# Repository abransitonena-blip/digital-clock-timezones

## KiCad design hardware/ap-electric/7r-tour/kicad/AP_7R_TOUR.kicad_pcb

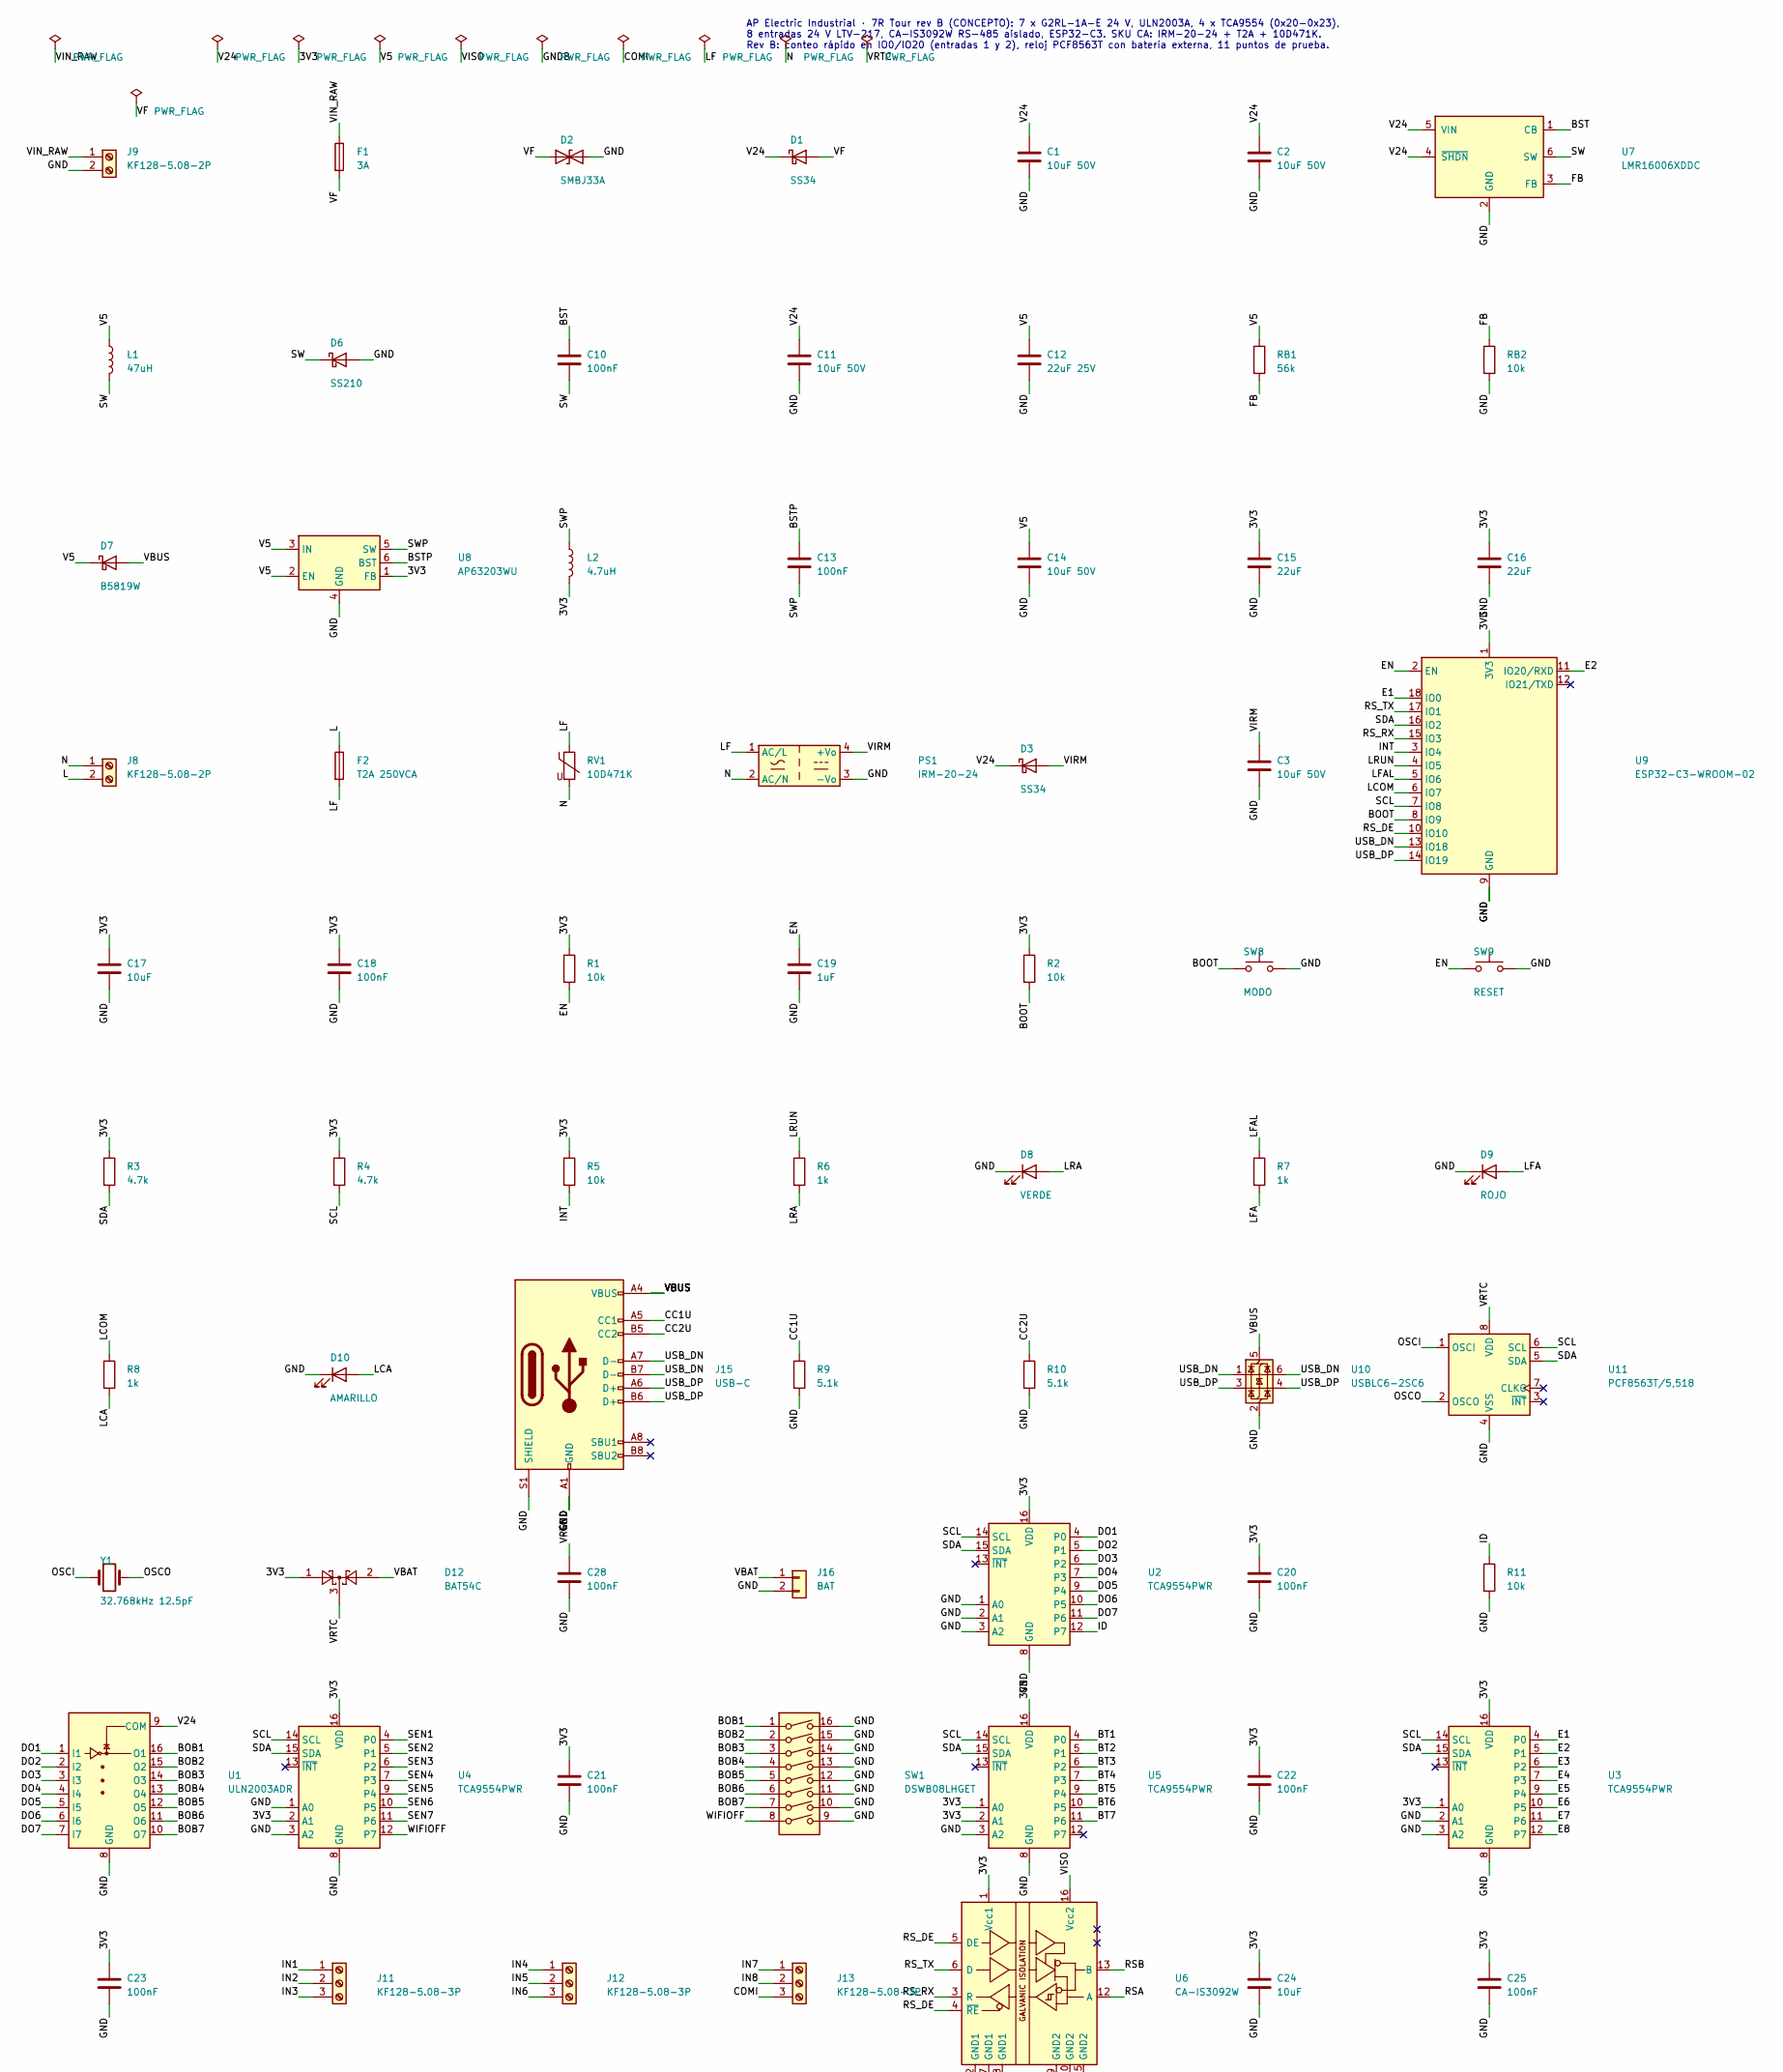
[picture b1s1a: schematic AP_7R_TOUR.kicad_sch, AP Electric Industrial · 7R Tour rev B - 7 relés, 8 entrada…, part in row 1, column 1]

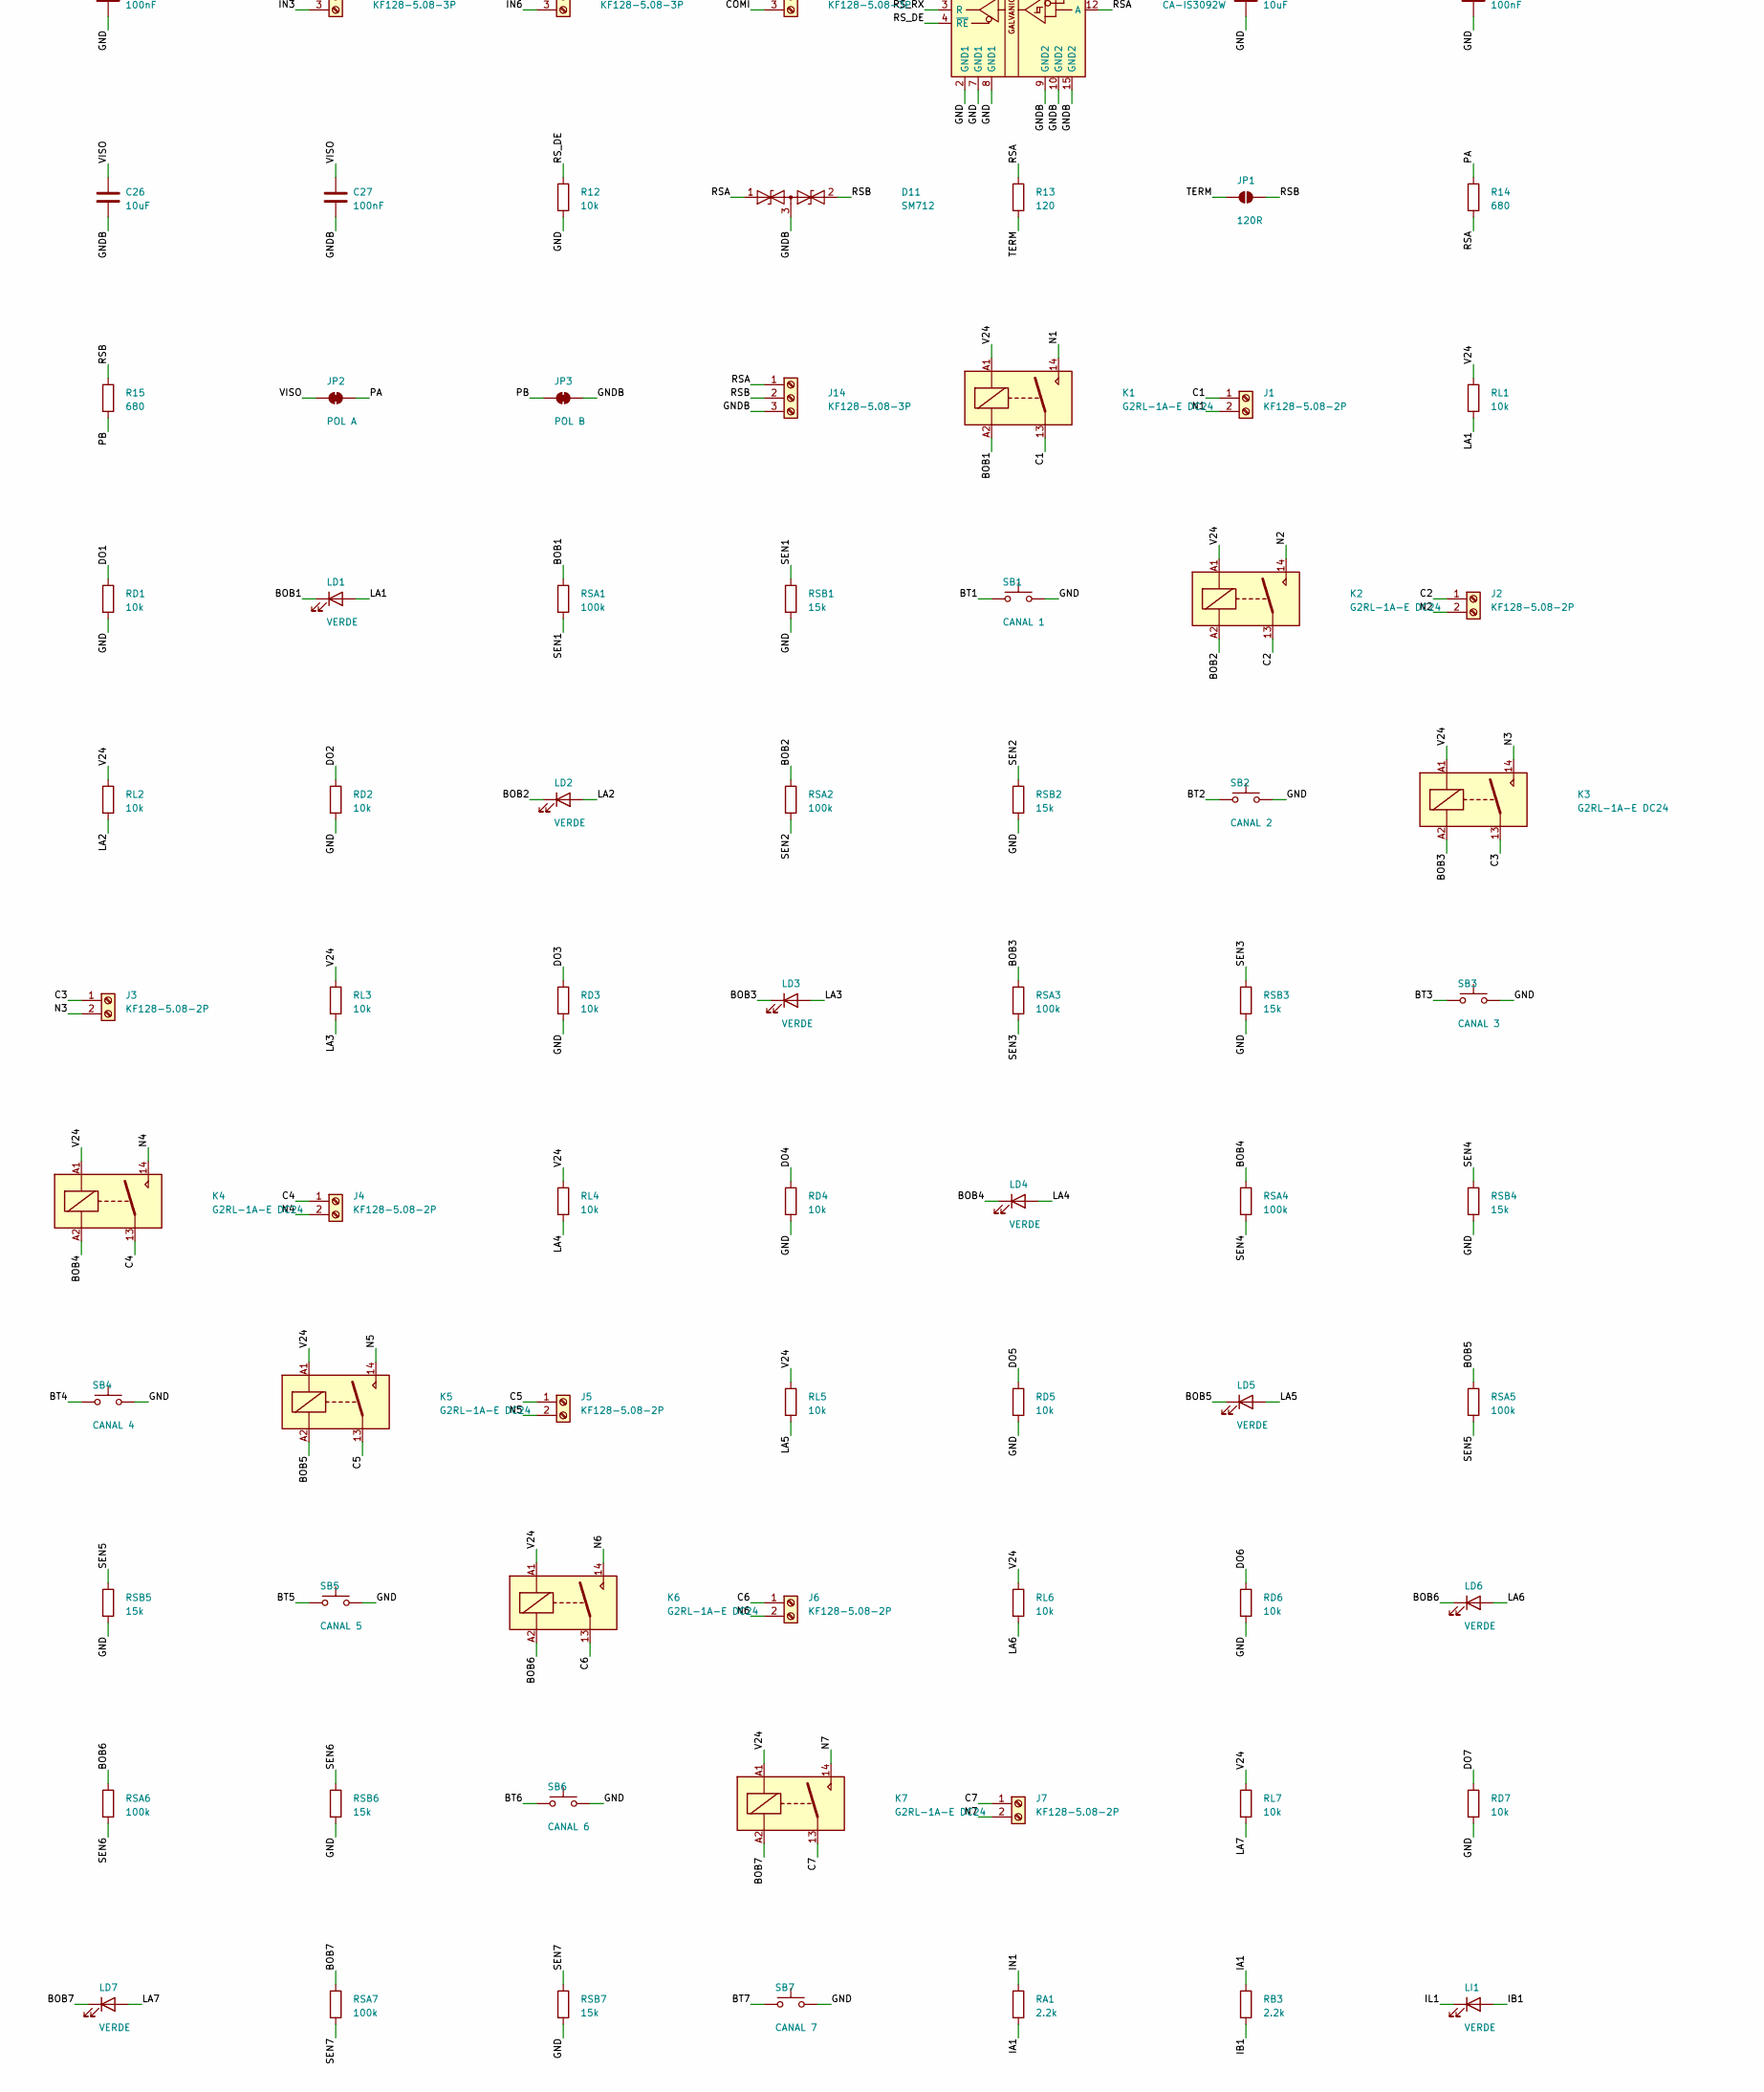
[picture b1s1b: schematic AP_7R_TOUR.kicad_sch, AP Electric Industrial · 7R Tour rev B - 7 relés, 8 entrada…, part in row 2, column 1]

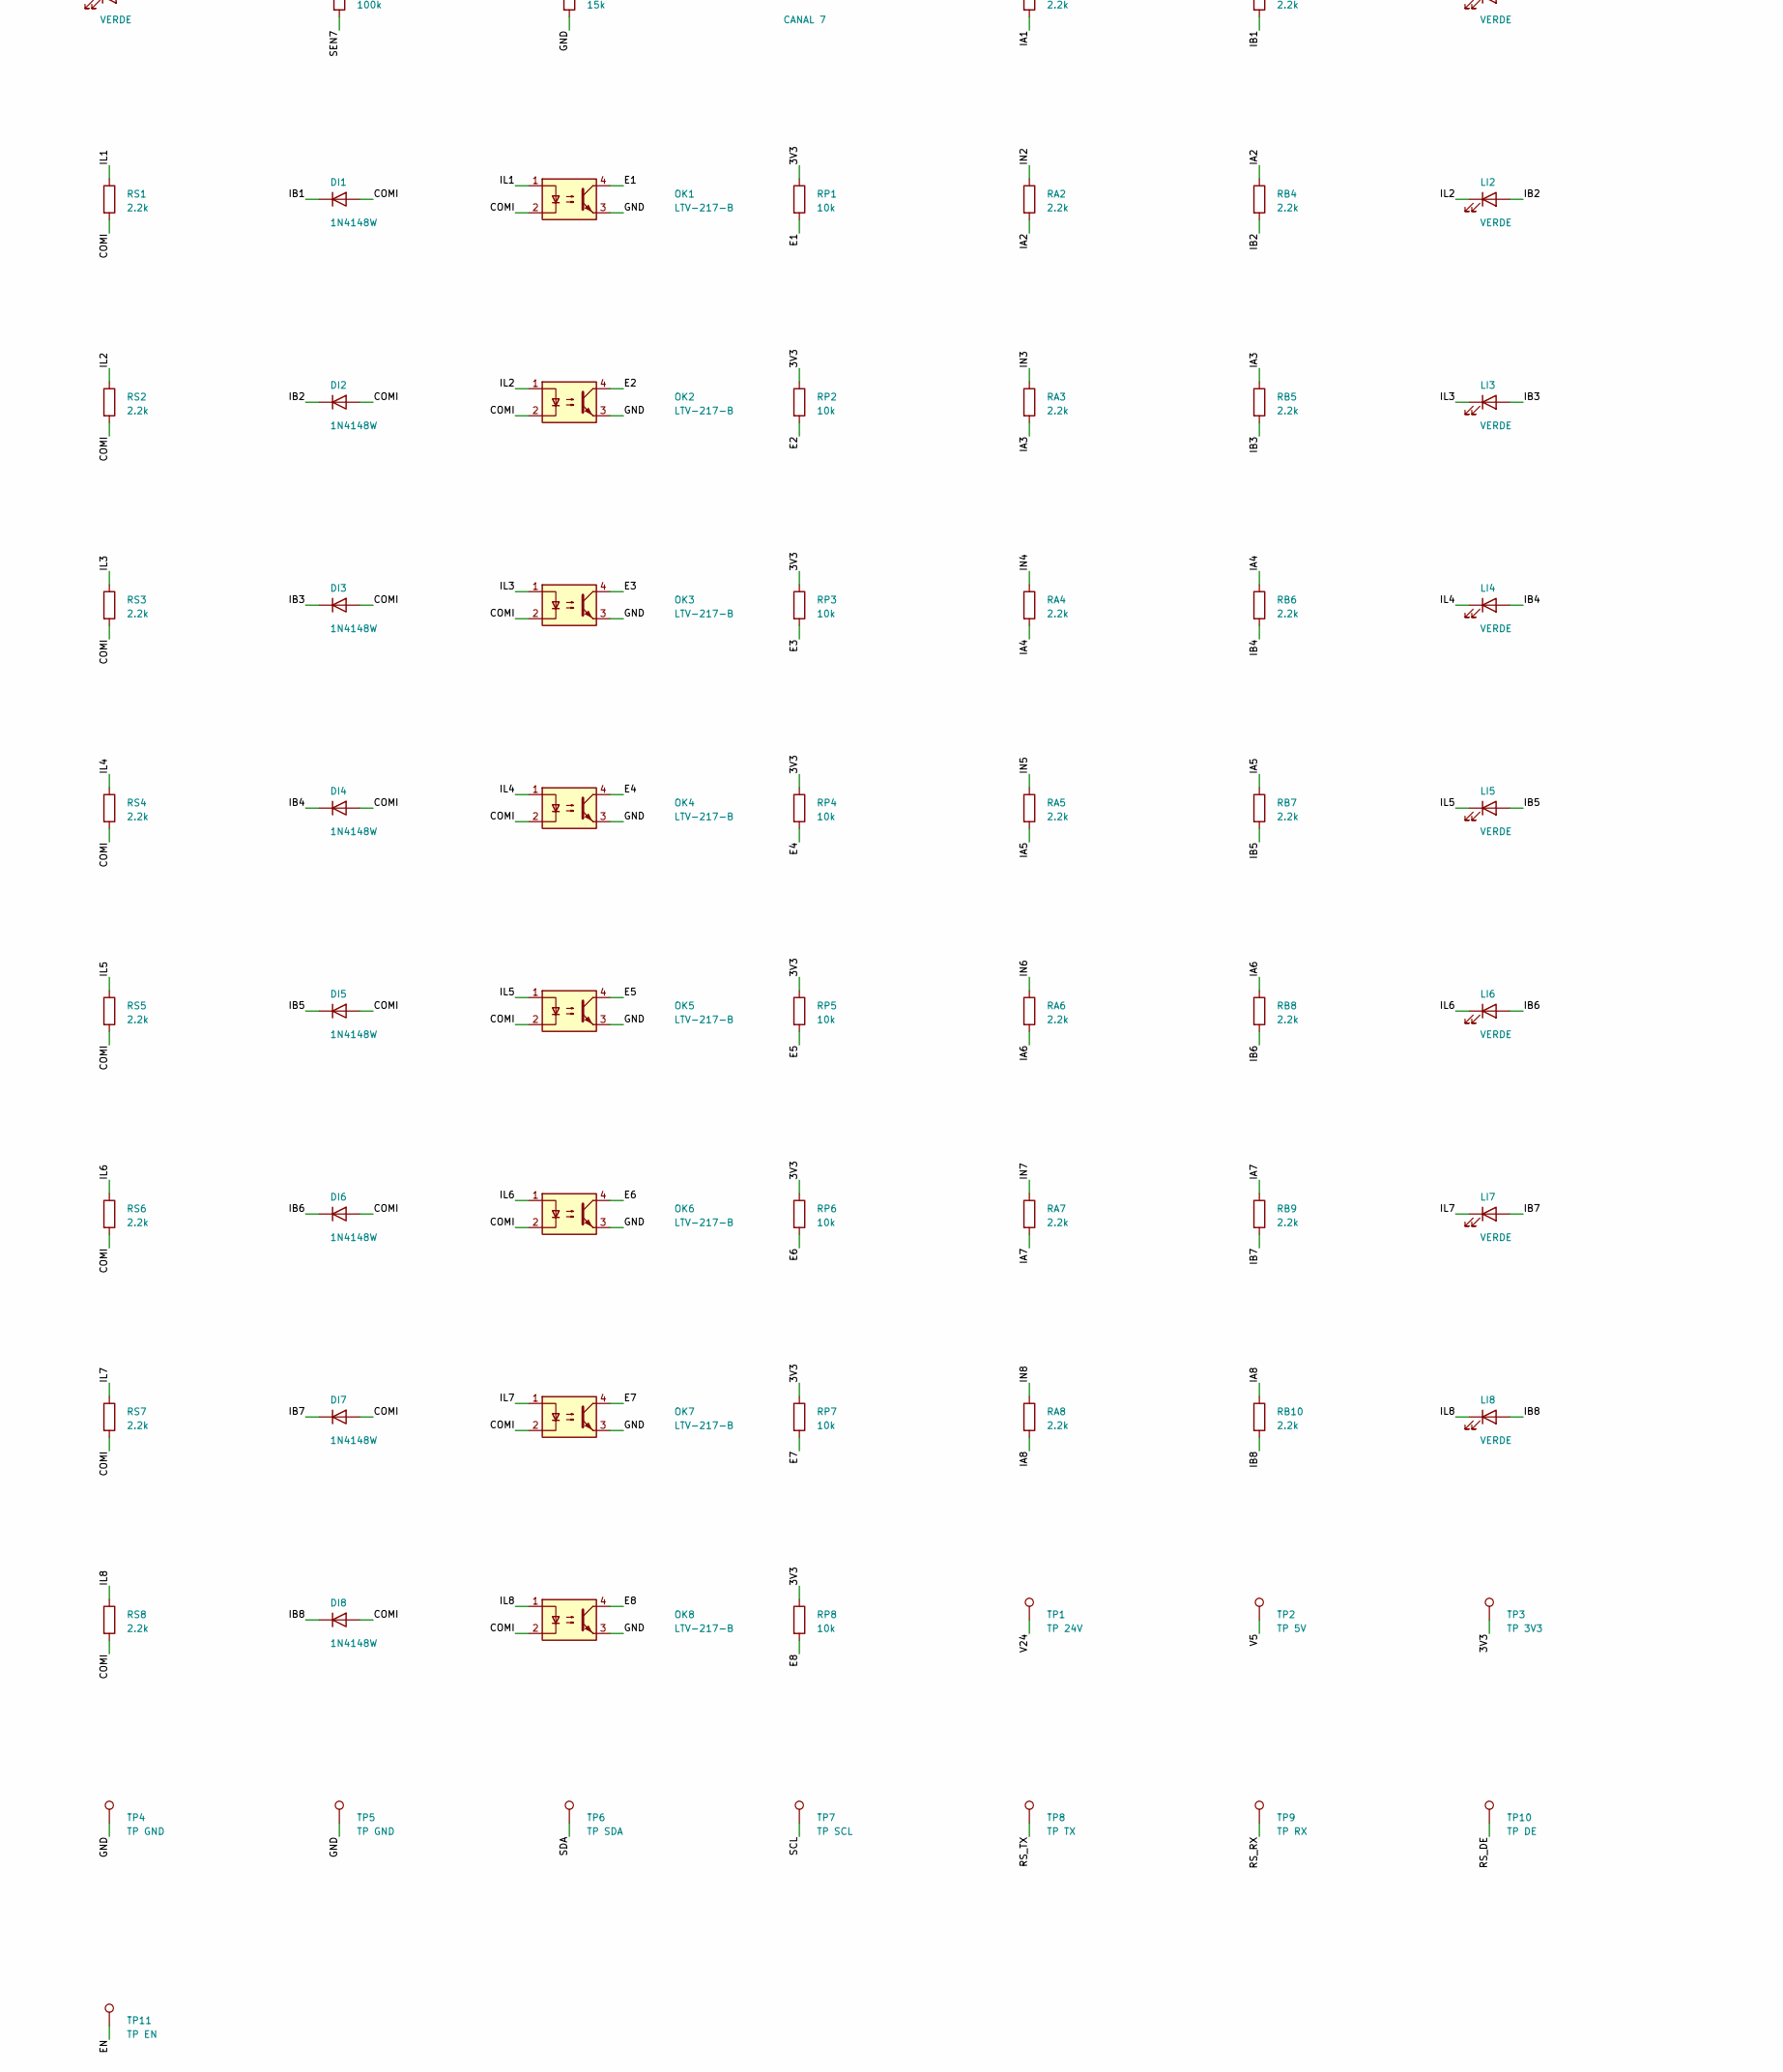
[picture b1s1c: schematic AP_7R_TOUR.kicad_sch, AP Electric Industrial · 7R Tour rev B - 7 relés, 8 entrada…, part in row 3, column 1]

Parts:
C1, C2, C3, C11, C14: 10uF 50V; C_1206_3216Metric
C10, C13, C18, C20, C21, C22, C23, C25, C27, C28: 100nF; C_0603_1608Metric
C12: 22uF 25V; C_1206_3216Metric
C15, C16: 22uF; C_0805_2012Metric
C17, C24, C26: 10uF; C_0805_2012Metric
C19: 1uF; C_0603_1608Metric
D1, D3: SS34; D_SMA
D2: SMBJ33A; D_SMB
D6: SS210; D_SMA
D7: B5819W; D_SOD-123
D8: VERDE; LED_0603_1608Metric
D9: ROJO; LED_0603_1608Metric
D10: AMARILLO; LED_0603_1608Metric
D11: SM712; SOT-23
D12: BAT54C; SOT-23
DI1, DI2, DI3, DI4, DI5, DI6, DI7, DI8: 1N4148W; D_SOD-123
F1: 3A; Fuse_1206_3216Metric
F2: T2A 250VCA; Fuse_2410_6125Metric
J1, J2, J3, J4, J5, J6, J7, J8, J9: KF128-5.08-2P; TerminalBlock_Phoenix_MKDS-1,5-2-5.08_1x02_P5.08mm_Horizont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
J11, J12, J13, J14: KF128-5.08-3P; TerminalBlock_Phoenix_MKDS-1,5-3-5.08_1x03_P5.08mm_Horizont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
J15: USB-C; USB_C_Receptacle_HRO_TYPE-C-31-M-12
J16: BAT; PinHeader_1x02_P2.54mm_Vertical
JP1: 120R; SolderJumper-2_P1.3mm_Open_RoundedPad1.0x1.5mm
JP2: POL A; SolderJumper-2_P1.3mm_Bridged_RoundedPad1.0x1.5mm
JP3: POL B; SolderJumper-2_P1.3mm_Bridged_RoundedPad1.0x1.5mm
K1, K2, K3, K4, K5, K6, K7: G2RL-1A-E DC24; Relay_SPST_Omron_G2RL-1A-E
L1: 47uH; L_Changjiang_FNR4030S
L2: 4.7uH; L_Changjiang_FNR4030S
LD1, LD2, LD3, LD4, LD5, LD6, LD7: VERDE; LED_0603_1608Metric
LI1, LI2, LI3, LI4, LI5, LI6, LI7, LI8: VERDE; LED_0603_1608Metric
OK1, OK2, OK3, OK4, OK5, OK6, OK7, OK8: LTV-217-B; SOP-4_4.4x2.6mm_P1.27mm
PS1: IRM-20-24; Converter_ACDC_MeanWell_IRM-20-xx_THT
R1, R2, R5, R11, R12: 10k; R_0603_1608Metric
R3, R4: 4.7k; R_0603_1608Metric
R6, R7, R8: 1k; R_0603_1608Metric
R9, R10: 5.1k; R_0603_1608Metric
R13: 120; R_1206_3216Metric
R14, R15: 680; R_0603_1608Metric
RA1, RA2, RA3, RA4, RA5, RA6, RA7, RA8: 2.2k; R_0805_2012Metric
RB1: 56k; R_0603_1608Metric
RB2: 10k; R_0603_1608Metric
RB3, RB4, RB5, RB6, RB7, RB8, RB9, RB10: 2.2k; R_0805_2012Metric
RD1, RD2, RD3, RD4, RD5, RD6, RD7: 10k; R_0603_1608Metric
RL1, RL2, RL3, RL4, RL5, RL6, RL7: 10k; R_0603_1608Metric
RP1, RP2, RP3, RP4, RP5, RP6, RP7, RP8: 10k; R_0603_1608Metric
RS1, RS2, RS3, RS4, RS5, RS6, RS7, RS8: 2.2k; R_0603_1608Metric
RSA1, RSA2, RSA3, RSA4, RSA5, RSA6, RSA7: 100k; R_0603_1608Metric
RSB1, RSB2, RSB3, RSB4, RSB5, RSB6, RSB7: 15k; R_0603_1608Metric
RV1: 10D471K; RV_Disc_D12mm_W5mm_P7.5mm
SB1: CANAL 1; SW_Push_1P1T_XKB_TS-1187A
SB2: CANAL 2; SW_Push_1P1T_XKB_TS-1187A
SB3: CANAL 3; SW_Push_1P1T_XKB_TS-1187A
SB4: CANAL 4; SW_Push_1P1T_XKB_TS-1187A
SB5: CANAL 5; SW_Push_1P1T_XKB_TS-1187A
SB6: CANAL 6; SW_Push_1P1T_XKB_TS-1187A
SB7: CANAL 7; SW_Push_1P1T_XKB_TS-1187A
SW1: DSWB08LHGET; SW_DIP_SPSTx08_Slide_9.78x22.5mm_W7.62mm_P2.54mm
SW8: MODO; SW_Push_1P1T_XKB_TS-1187A
SW9: RESET; SW_Push_1P1T_XKB_TS-1187A
TP1: TP 24V; TestPoint_Pad_D1.5mm
TP2: TP 5V; TestPoint_Pad_D1.5mm
TP3: TP 3V3; TestPoint_Pad_D1.5mm
TP4, TP5: TP GND; TestPoint_Pad_D1.5mm
TP6: TP SDA; TestPoint_Pad_D1.5mm
TP7: TP SCL; TestPoint_Pad_D1.5mm
TP8: TP TX; TestPoint_Pad_D1.5mm
TP9: TP RX; TestPoint_Pad_D1.5mm
TP10: TP DE; TestPoint_Pad_D1.5mm
TP11: TP EN; TestPoint_Pad_D1.5mm
U1: ULN2003ADR; SOIC-16_3.9x9.9mm_P1.27mm
U2, U3, U4, U5: TCA9554PWR; TSSOP-16_4.4x5mm_P0.65mm
U6: CA-IS3092W; SOIC-16W_7.5x10.3mm_P1.27mm
U7: LMR16006XDDC; SOT-23-6
U8: AP63203WU; TSOT-23-6
U9: ESP32-C3-WROOM-02; ESP32-C3-WROOM-02_JLC
U10: USBLC6-2SC6; SOT-23-6
U11: PCF8563T/5,518; SOIC-8_3.9x4.9mm_P1.27mm
Y1: 32.768kHz 12.5pF; Crystal_SMD_3215-2Pin_3.2x1.5mm

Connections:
/3V3: C15.1, C16.1, C17.1, C18.1, C20.1, C21.1, C22.1, C23.1, C24.1, C25.1, D12.1, L2.2, R1.1, R2.1, R3.1, R4.1, R5.1, RP1.1, RP2.1, RP3.1, RP4.1, RP5.1, RP6.1, RP7.1, RP8.1, TP3.1, U2.16 (VDD), U3.1 (A0), U3.16 (VDD), U4.2 (A1), U4.16 (VDD), U5.1 (A0), U5.2 (A1), U5.16 (VDD), U6.1 (Vcc1), U8.1 (FB), U9.1 (3V3)
/BOB1: K1.A2, LD1.1 (K), RSA1.1, SW1.1, U1.16 (O1)
/BOB2: K2.A2, LD2.1 (K), RSA2.1, SW1.2, U1.15 (O2)
/BOB3: K3.A2, LD3.1 (K), RSA3.1, SW1.3, U1.14 (O3)
/BOB4: K4.A2, LD4.1 (K), RSA4.1, SW1.4, U1.13 (O4)
/BOB5: K5.A2, LD5.1 (K), RSA5.1, SW1.5, U1.12 (O5)
/BOB6: K6.A2, LD6.1 (K), RSA6.1, SW1.6, U1.11 (O6)
/BOB7: K7.A2, LD7.1 (K), RSA7.1, SW1.7, U1.10 (O7)
/BOOT: R2.2, SW8.1, U9.8 (IO9)
/BST: C10.1, U7.1 (CB)
/BSTP: C13.1, U8.6 (BST)
/BT1: SB1.1, U5.4 (P0)
/BT2: SB2.1, U5.5 (P1)
/BT3: SB3.1, U5.6 (P2)
/BT4: SB4.1, U5.7 (P3)
/BT5: SB5.1, U5.9 (P4)
/BT6: SB6.1, U5.10 (P5)
/BT7: SB7.1, U5.11 (P6)
/C1: J1.1, K1.13
/C2: J2.1, K2.13
/C3: J3.1, K3.13
/C4: J4.1, K4.13
/C5: J5.1, K5.13
/C6: J6.1, K6.13
/C7: J7.1, K7.13
/CC1U: J15.A5 (CC1), R9.1
/CC2U: J15.B5 (CC2), R10.1
/COMI: DI1.2 (A), DI2.2 (A), DI3.2 (A), DI4.2 (A), DI5.2 (A), DI6.2 (A), DI7.2 (A), DI8.2 (A), J13.3, OK1.2, OK2.2, OK3.2, OK4.2, OK5.2, OK6.2, OK7.2, OK8.2, RS1.2, RS2.2, RS3.2, RS4.2, RS5.2, RS6.2, RS7.2, RS8.2
/DO1: RD1.1, U1.1 (I1), U2.4 (P0)
/DO2: RD2.1, U1.2 (I2), U2.5 (P1)
/DO3: RD3.1, U1.3 (I3), U2.6 (P2)
/DO4: RD4.1, U1.4 (I4), U2.7 (P3)
/DO5: RD5.1, U1.5 (I5), U2.9 (P4)
/DO6: RD6.1, U1.6 (I6), U2.10 (P5)
/DO7: RD7.1, U1.7 (I7), U2.11 (P6)
/E1: OK1.4, RP1.2, U3.4 (P0), U9.18 (IO0)
/E2: OK2.4, RP2.2, U3.5 (P1), U9.11 (IO20/RXD)
/E3: OK3.4, RP3.2, U3.6 (P2)
/E4: OK4.4, RP4.2, U3.7 (P3)
/E5: OK5.4, RP5.2, U3.9 (P4)
/E6: OK6.4, RP6.2, U3.10 (P5)
/E7: OK7.4, RP7.2, U3.11 (P6)
/E8: OK8.4, RP8.2, U3.12 (P7)
/EN: C19.1, R1.2, SW9.1, TP11.1, U9.2 (EN)
/FB: RB1.2, RB2.1, U7.3 (FB)
/GND: C1.2, C2.2, C3.2, C11.2, C12.2, C14.2, C15.2, C16.2, C17.2, C18.2, C19.2, C20.2, C21.2, C22.2, C23.2, C24.2, C25.2, C28.2, D2.2 (A2), D6.2 (A), D8.1 (K), D9.1 (K), D10.1 (K), J9.2, J15.A1 (GND), J15.A12 (GND), J15.B1 (GND), J15.B12 (GND), J15.S1 (SHIELD), J16.2, OK1.3, OK2.3, OK3.3, OK4.3, OK5.3, OK6.3, OK7.3, OK8.3, PS1.3 (-Vo), R9.2, R10.2, R11.2, R12.2, RB2.2, RD1.2, RD2.2, RD3.2, RD4.2, RD5.2, RD6.2, RD7.2, RSB1.2, RSB2.2, RSB3.2, RSB4.2, RSB5.2, RSB6.2, RSB7.2, SB1.2, SB2.2, SB3.2, SB4.2, SB5.2, SB6.2, SB7.2, SW1.9, SW1.10, SW1.11, SW1.12, SW1.13, SW1.14, SW1.15, SW1.16, SW8.2, SW9.2, TP4.1, TP5.1, U1.8 (GND), U2.1 (A0), U2.2 (A1), U2.3 (A2), U2.8 (GND), U3.2 (A1), U3.3 (A2), U3.8 (GND), U4.1 (A0), U4.3 (A2), U4.8 (GND), U5.3 (A2), U5.8 (GND), U6.2 (GND1), U6.7 (GND1), U6.8 (GND1), U7.2 (GND), U8.4 (GND), U9.9 (GND), U9.19 (GND), U10.2 (GND), U11.4 (VSS)
/GNDB: C26.2, C27.2, D11.3 (common), J14.3, JP3.2 (B), U6.9 (GND2), U6.10 (GND2), U6.15 (GND2)
/IA1: RA1.2, RB3.1
/IA2: RA2.2, RB4.1
/IA3: RA3.2, RB5.1
/IA4: RA4.2, RB6.1
/IA5: RA5.2, RB7.1
/IA6: RA6.2, RB8.1
/IA7: RA7.2, RB9.1
/IA8: RA8.2, RB10.1
/IB1: DI1.1 (K), LI1.2 (A), RB3.2
/IB2: DI2.1 (K), LI2.2 (A), RB4.2
/IB3: DI3.1 (K), LI3.2 (A), RB5.2
/IB4: DI4.1 (K), LI4.2 (A), RB6.2
/IB5: DI5.1 (K), LI5.2 (A), RB7.2
/IB6: DI6.1 (K), LI6.2 (A), RB8.2
/IB7: DI7.1 (K), LI7.2 (A), RB9.2
/IB8: DI8.1 (K), LI8.2 (A), RB10.2
/ID: R11.1, U2.12 (P7)
/IL1: LI1.1 (K), OK1.1, RS1.1
/IL2: LI2.1 (K), OK2.1, RS2.1
/IL3: LI3.1 (K), OK3.1, RS3.1
/IL4: LI4.1 (K), OK4.1, RS4.1
/IL5: LI5.1 (K), OK5.1, RS5.1
/IL6: LI6.1 (K), OK6.1, RS6.1
/IL7: LI7.1 (K), OK7.1, RS7.1
/IL8: LI8.1 (K), OK8.1, RS8.1
/IN1: J11.1, RA1.1
/IN2: J11.2, RA2.1
/IN3: J11.3, RA3.1
/IN4: J12.1, RA4.1
/IN5: J12.2, RA5.1
/IN6: J12.3, RA6.1
/IN7: J13.1, RA7.1
/IN8: J13.2, RA8.1
/INT: R5.2, U9.3 (IO4)
/L: F2.1, J8.2
/LA1: LD1.2 (A), RL1.2
/LA2: LD2.2 (A), RL2.2
/LA3: LD3.2 (A), RL3.2
/LA4: LD4.2 (A), RL4.2
/LA5: LD5.2 (A), RL5.2
/LA6: LD6.2 (A), RL6.2
/LA7: LD7.2 (A), RL7.2
/LCA: D10.2 (A), R8.2
/LCOM: R8.1, U9.6 (IO7)
/LF: F2.2, PS1.1 (AC/L), RV1.1
/LFA: D9.2 (A), R7.2
/LFAL: R7.1, U9.5 (IO6)
/LRA: D8.2 (A), R6.2
/LRUN: R6.1, U9.4 (IO5)
/N: J8.1, PS1.2 (AC/N), RV1.2
/N1: J1.2, K1.14
/N2: J2.2, K2.14
/N3: J3.2, K3.14
/N4: J4.2, K4.14
/N5: J5.2, K5.14
/N6: J6.2, K6.14
/N7: J7.2, K7.14
/OSCI: U11.1 (OSCI), Y1.1
/OSCO: U11.2 (OSCO), Y1.2
/PA: JP2.2 (B), R14.1
/PB: JP3.1 (A), R15.2
/RSA: D11.1 (A1), J14.1, R13.1, R14.2, U6.12 (A)
/RSB: D11.2 (A2), J14.2, JP1.2 (B), R15.1, U6.13 (B)
/RS_DE: R12.1, TP10.1, U6.4 (~RE), U6.5 (DE), U9.10 (IO10)
/RS_RX: TP9.1, U6.3 (R), U9.15 (IO3)
/RS_TX: TP8.1, U6.6 (D), U9.17 (IO1)
/SCL: R4.2, TP7.1, U2.14 (SCL), U3.14 (SCL), U4.14 (SCL), U5.14 (SCL), U9.7 (IO8), U11.6 (SCL)
/SDA: R3.2, TP6.1, U2.15 (SDA), U3.15 (SDA), U4.15 (SDA), U5.15 (SDA), U9.16 (IO2), U11.5 (SDA)
/SEN1: RSA1.2, RSB1.1, U4.4 (P0)
/SEN2: RSA2.2, RSB2.1, U4.5 (P1)
/SEN3: RSA3.2, RSB3.1, U4.6 (P2)
/SEN4: RSA4.2, RSB4.1, U4.7 (P3)
/SEN5: RSA5.2, RSB5.1, U4.9 (P4)
/SEN6: RSA6.2, RSB6.1, U4.10 (P5)
/SEN7: RSA7.2, RSB7.1, U4.11 (P6)
/SW: C10.2, D6.1 (K), L1.2, U7.6 (SW)
/SWP: C13.2, L2.1, U8.5 (SW)
/TERM: JP1.1 (A), R13.2
/USB_DN: J15.A7 (D-), J15.B7 (D-), U9.13 (IO18), U10.1 (I/O1), U10.6 (I/O1)
/USB_DP: J15.A6 (D+), J15.B6 (D+), U9.14 (IO19), U10.3 (I/O2), U10.4 (I/O2)
/V5: C12.1, C14.1, D7.1 (K), L1.1, RB1.1, TP2.1, U8.2 (EN), U8.3 (IN)
/V24: C1.1, C2.1, C11.1, D1.1 (K), D3.1 (K), K1.A1, K2.A1, K3.A1, K4.A1, K5.A1, K6.A1, K7.A1, RL1.1, RL2.1, RL3.1, RL4.1, RL5.1, RL6.1, RL7.1, TP1.1, U1.9 (COM), U7.4 (~SHDN), U7.5 (VIN)
/VBAT: D12.2, J16.1
/VBUS: D7.2 (A), J15.A4 (VBUS), J15.A9 (VBUS), J15.B4 (VBUS), J15.B9 (VBUS), U10.5 (VBUS)
/VF: D1.2 (A), D2.1 (A1), F1.2
/VIN_RAW: F1.1, J9.1
/VIRM: C3.1, D3.2 (A), PS1.4 (+Vo)
/VISO: C26.1, C27.1, JP2.1 (A), U6.16 (Vcc2)
/VRTC: C28.1, D12.3, U11.8 (VDD)
/WIFIOFF: SW1.8, U4.12 (P7)

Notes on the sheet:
AP Electric Industrial · 7R Tour rev B (CONCEPTO): 7 x G2RL-1A-E 24 V, ULN2003A, 4 x TCA9554 (0x20-0x23), 8 entradas 24 V LTV-217, CA-IS3092W RS-485 aislado, ESP32-C3. SKU CA: IRM-20-24 + T2A + 10D471K. Rev B: conteo rápido en IO0/IO20 (entradas 1 y 2), reloj PCF8563T con batería externa, 11 puntos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

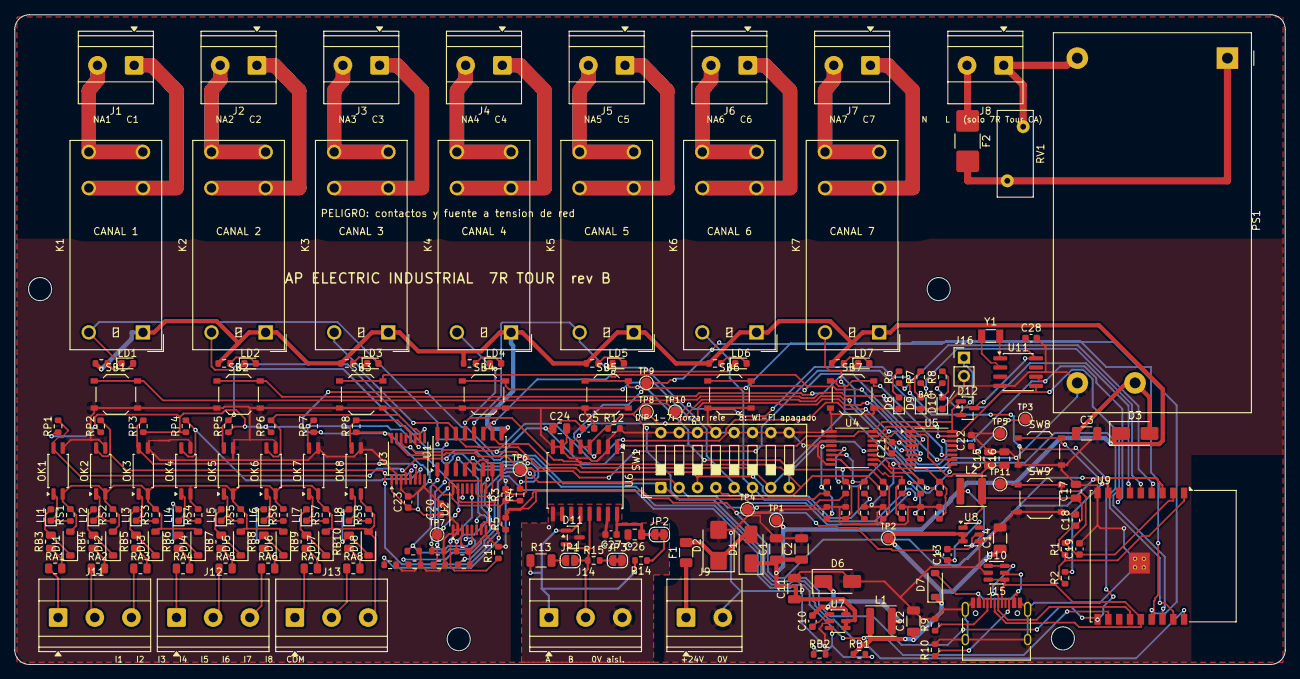
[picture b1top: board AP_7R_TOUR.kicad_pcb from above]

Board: 2 copper layers, 176.0 x 90.0 mm, 208 parts (0 on the bottom side), 137 nets.

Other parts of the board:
H1, H2, H3, H4: MountingHole_3.2mm_M3

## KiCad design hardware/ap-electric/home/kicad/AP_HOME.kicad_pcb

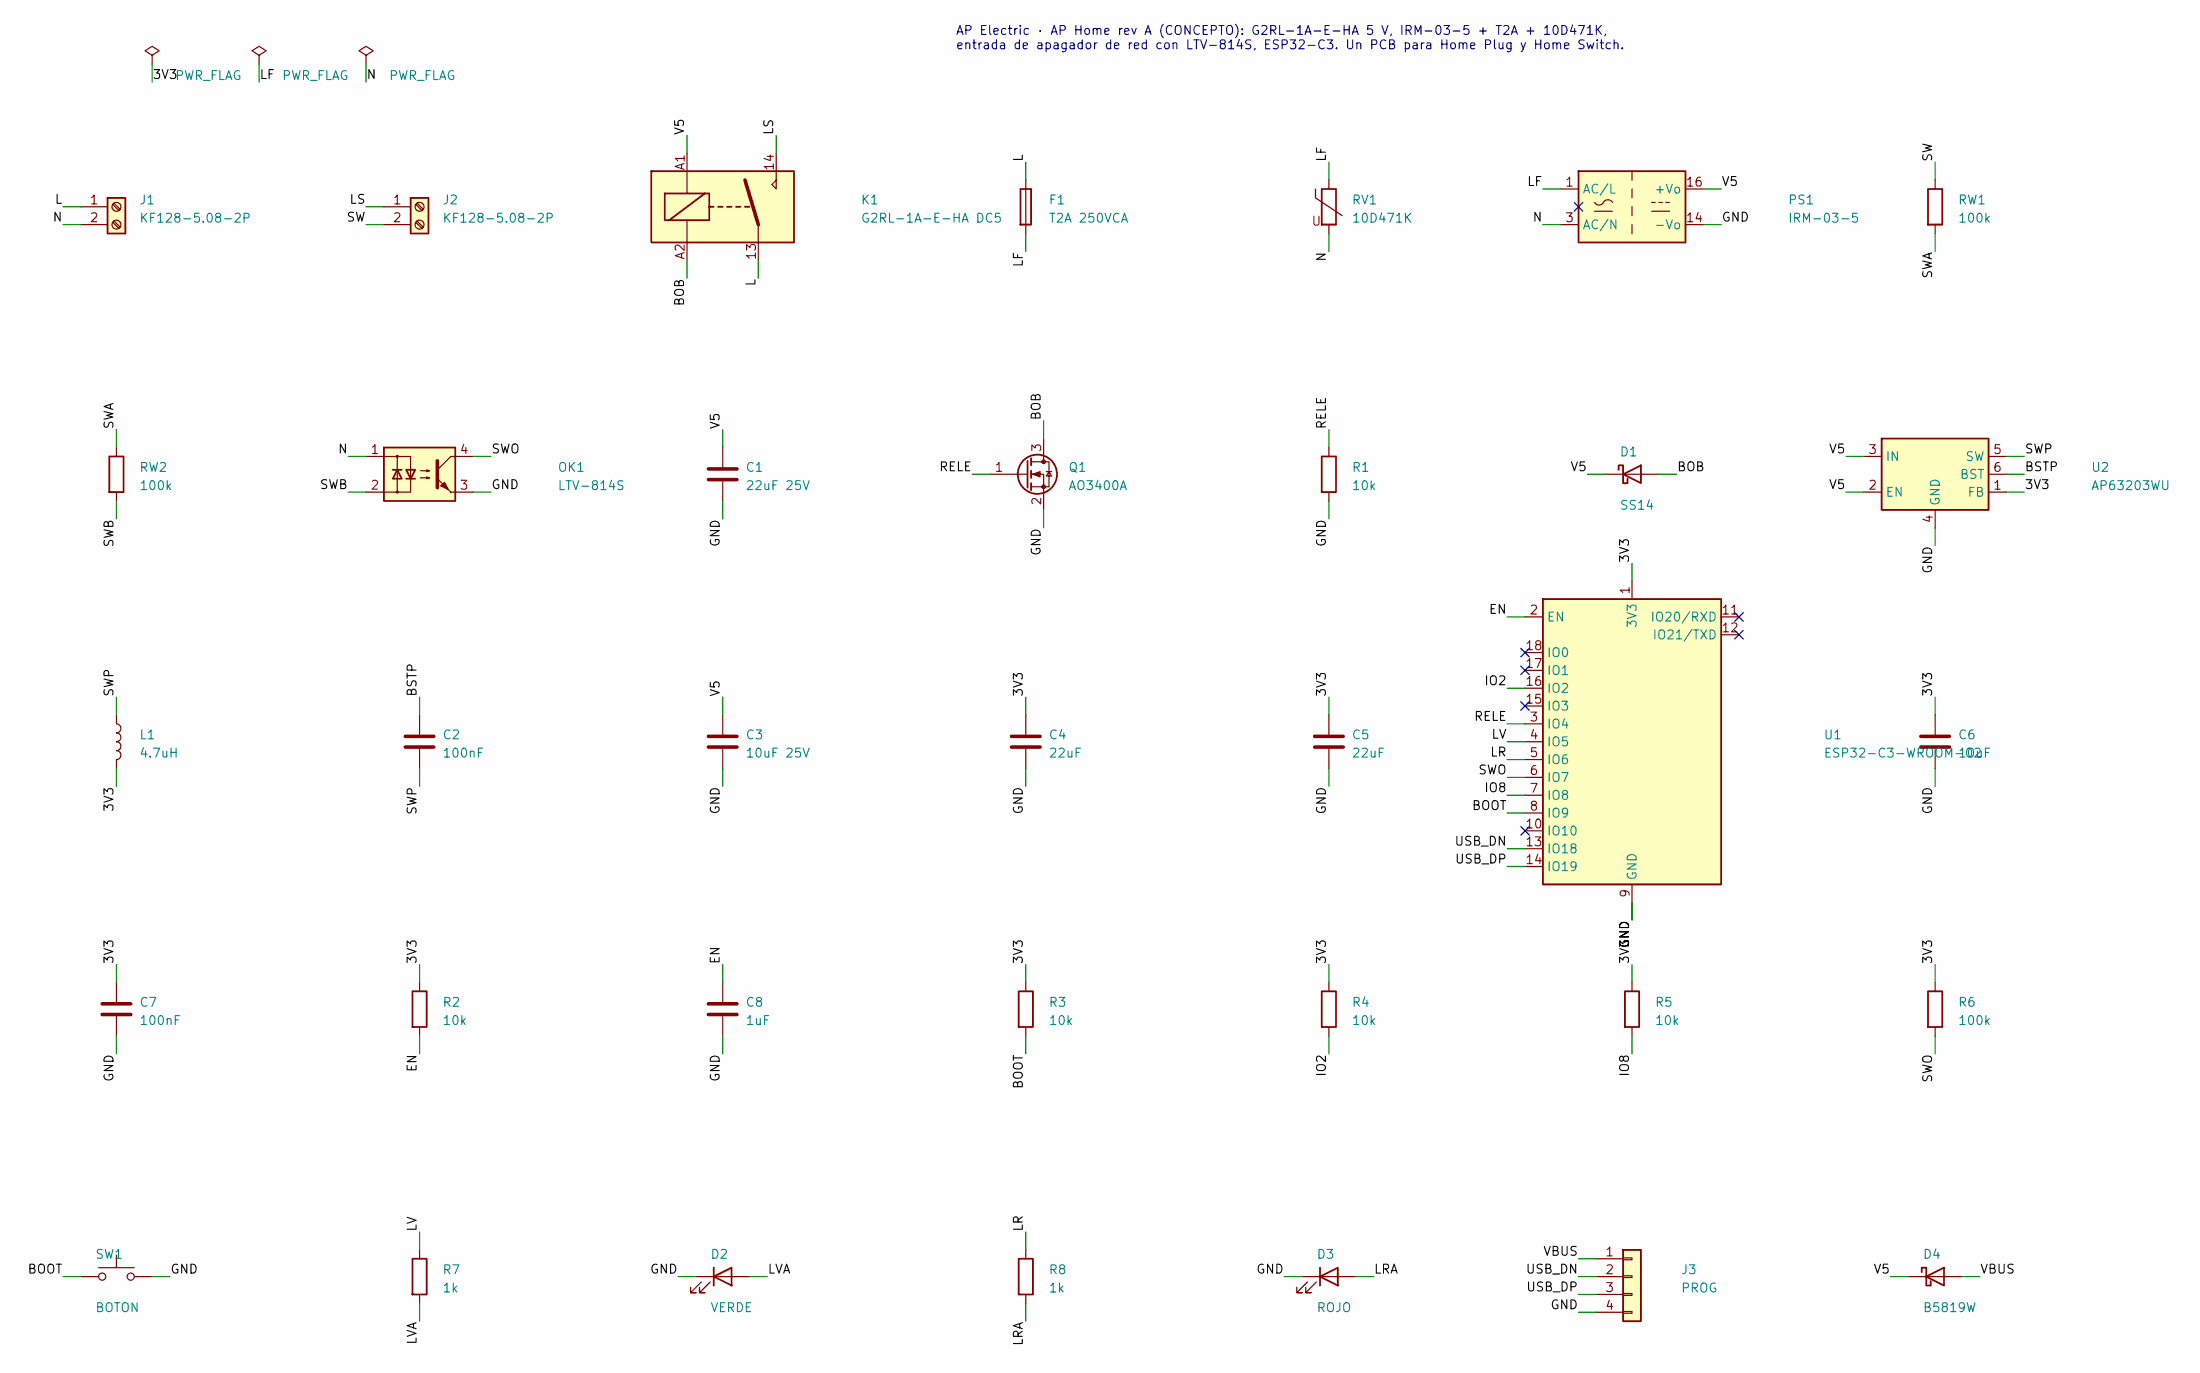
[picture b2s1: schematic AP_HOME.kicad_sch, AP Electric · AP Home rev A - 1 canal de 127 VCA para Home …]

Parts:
C1: 22uF 25V; C_1206_3216Metric
C2, C7: 100nF; C_0603_1608Metric
C3: 10uF 25V; C_1206_3216Metric
C4, C5: 22uF; C_0805_2012Metric
C6: 10uF; C_0805_2012Metric
C8: 1uF; C_0603_1608Metric
D1: SS14; D_SMA
D2: VERDE; LED_0603_1608Metric
D3: ROJO; LED_0603_1608Metric
D4: B5819W; D_SOD-123
F1: T2A 250VCA; Fuse_2410_6125Metric
J1, J2: KF128-5.08-2P; TerminalBlock_Phoenix_MKDS-1,5-2-5.08_1x02_P5.08mm_Horizont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
J3: PROG; PinHeader_1x04_P2.54mm_Vertical
K1: G2RL-1A-E-HA DC5; Relay_SPST_Omron_G2RL-1A-E
L1: 4.7uH; L_Changjiang_FNR4030S
OK1: LTV-814S; SMDIP-4_W9.53mm
PS1: IRM-03-5; Converter_ACDC_MeanWell_IRM-03-xx_THT
Q1: AO3400A; SOT-23
R1, R2, R3, R4, R5: 10k; R_0603_1608Metric
R6: 100k; R_0603_1608Metric
R7, R8: 1k; R_0603_1608Metric
RV1: 10D471K; RV_Disc_D12mm_W5mm_P7.5mm
RW1, RW2: 100k; R_1206_3216Metric
SW1: BOTON; SW_Push_1P1T_XKB_TS-1187A
U1: ESP32-C3-WROOM-02; ESP32-C3-WROOM-02_JLC
U2: AP63203WU; TSOT-23-6

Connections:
/3V3: C4.1, C5.1, C6.1, C7.1, L1.2, R2.1, R3.1, R4.1, R5.1, R6.1, U1.1 (3V3), U2.1 (FB)
/BOB: D1.2 (A), K1.A2, Q1.3 (D)
/BOOT: R3.2, SW1.1, U1.8 (IO9)
/BSTP: C2.1, U2.6 (BST)
/EN: C8.1, R2.2, U1.2 (EN)
/GND: C1.2, C3.2, C4.2, C5.2, C6.2, C7.2, C8.2, D2.1 (K), D3.1 (K), J3.4, OK1.3, PS1.14 (-Vo), Q1.2 (S), R1.2, SW1.2, U1.9 (GND), U1.19 (GND), U2.4 (GND)
/IO2: R4.2, U1.16 (IO2)
/IO8: R5.2, U1.7 (IO8)
/L: F1.1, J1.1, K1.13
/LF: F1.2, PS1.1 (AC/L), RV1.1
/LR: R8.1, U1.5 (IO6)
/LRA: D3.2 (A), R8.2
/LS: J2.1, K1.14
/LV: R7.1, U1.4 (IO5)
/LVA: D2.2 (A), R7.2
/N: J1.2, OK1.1, PS1.3 (AC/N), RV1.2
/RELE: Q1.1 (G), R1.1, U1.3 (IO4)
/SW: J2.2, RW1.1
/SWA: RW1.2, RW2.1
/SWB: OK1.2, RW2.2
/SWO: OK1.4, R6.2, U1.6 (IO7)
/SWP: C2.2, L1.1, U2.5 (SW)
/USB_DN: J3.2, U1.13 (IO18)
/USB_DP: J3.3, U1.14 (IO19)
/V5: C1.1, C3.1, D1.1 (K), D4.1 (K), K1.A1, PS1.16 (+Vo), U2.2 (EN), U2.3 (IN)
/VBUS: D4.2 (A), J3.1

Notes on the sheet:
AP Electric · AP Home rev A (CONCEPTO): G2RL-1A-E-HA 5 V, IRM-03-5 + T2A + 10D471K, entrada de apagador de red con LTV-814S, ESP32-C3. Un PCB para Home Plug y Home Switch.
